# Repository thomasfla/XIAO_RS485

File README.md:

# XIAO_RS485
XIAO with RS485 tranceiver 50Mbps

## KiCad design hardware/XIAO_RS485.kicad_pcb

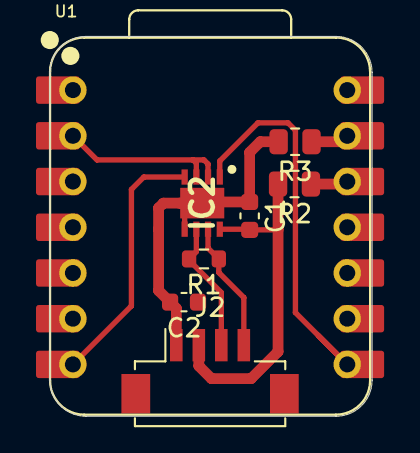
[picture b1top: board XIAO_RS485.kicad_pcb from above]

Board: 2 copper layers, 17.9 x 21.1 mm, 8 parts (0 on the bottom side), 9 nets.

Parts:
C1, C2: C; C_0603_1608Metric
IC2: THVD2450DRBR; SON65P300X300X100-9N
J2: Conn_01x04_Pin; Hirose_DF13C_CL535-0404-8-51_1x04-1MP_P1.25mm_Vertical
R1: 120; R_0603_1608Metric
R2, R3: R; R_0805_2012Metric
U1: Seeed Studio XIAO SAMD21; XIAO-ESP32-S3-DIP

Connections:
+3.3V: C1.2, C2.1, IC2.8 (VCC), J2.2, R2.2
/OE0: IC2.2 (~RE), IC2.3 (DE), U1.2 (PA4_A1_D1)
/RX0: IC2.1 (R), U1.8 (PB09_A7_D7_RX)
/TX0: IC2.4 (D), U1.7 (PB08_A6_D6_TX)
GND: C1.1, C2.2, IC2.5 (GND_1), IC2.9 (GND_2), J2.1, R3.2
unnamed: IC2.6 (A), J2.3, R1.2
unnamed: IC2.7 (B), J2.4, R1.1
unnamed: R3.1, U1.13 (GND)
unnamed: R2.1, U1.12 (3V3)

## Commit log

2024-11-12 add hardware files
